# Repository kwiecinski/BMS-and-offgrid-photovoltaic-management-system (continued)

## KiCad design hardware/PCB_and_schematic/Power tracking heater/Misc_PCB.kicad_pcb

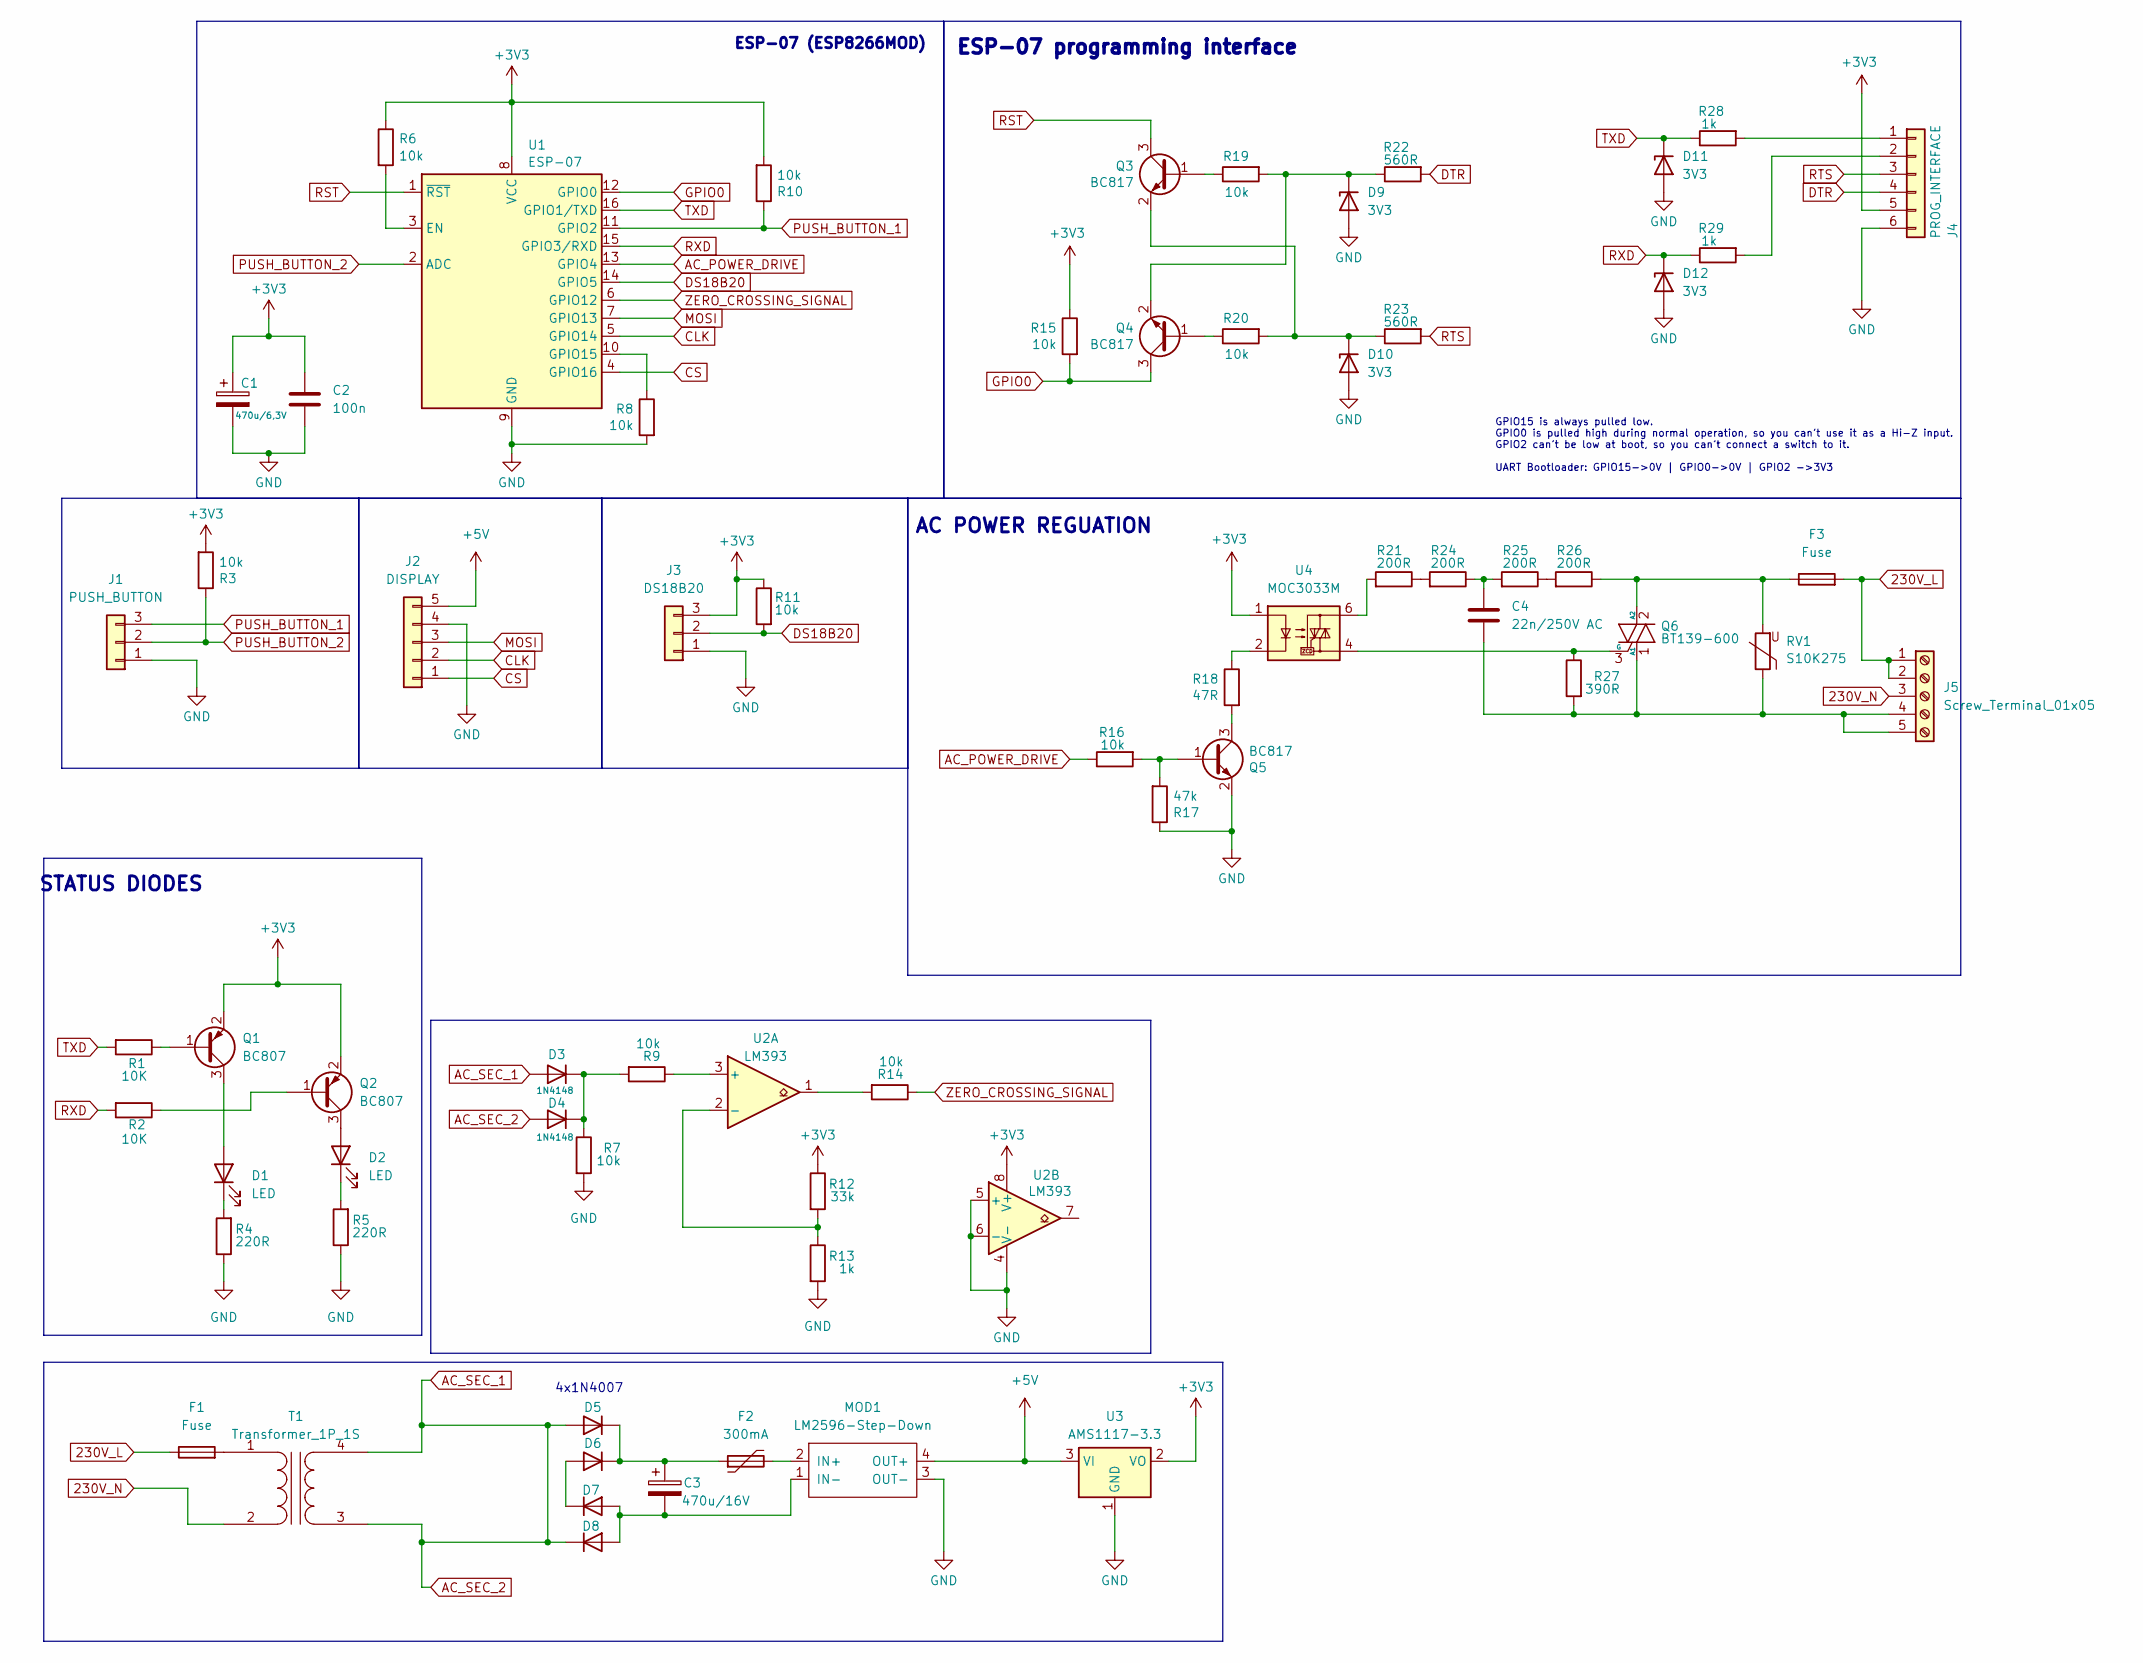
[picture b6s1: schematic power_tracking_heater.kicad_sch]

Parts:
C1: 470u/6,3V; CP_Elec_5x5.7
C2: 100n; C_0805_2012Metric
C3: 470u/16V; CP_Elec_5x5.7
C4: 22n/250V AC; C_Rect_L16.5mm_W6.0mm_P15.00mm_MKT
D1, D2: LED; LED_PLCC-2_3.4x3.0mm_KA
D3, D4: 1N4148; D_DO-35_SOD27_P7.62mm_Horizontal
D5, D6, D7, D8: 1N4007; DO-213AB_1-mediana
D9, D10, D11, D12: 3V3; D_MiniMELF
F1, F3: Fuse; Fuseholder_Clip-5x20mm_Eaton_1A5601-01_Inline_P20.80x6.76mm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
F2: 300mA; Fuse_2010_5025Metric
J1: PUSH_BUTTON; PinSocket_1x03_P2.54mm_Vertical
J2: DISPLAY; JST_XA_B05B-XASK-1_1x05_P2.50mm_Vertical
J3: DS18B20; JST_XA_B03B-XASK-1_1x03_P2.50mm_Vertical
J4: PROG_INTERFACE; Conn-01x06
J5: Screw_Terminal_01x05; Screw-Terminal-5.00mm-5pin
MOD1: LM2596-Step-Down; MP1504_Mini_3A_Step_Down_Conv
Q1, Q2: BC807; SOT-23
Q3, Q4, Q5: BC817; SOT-23
Q6: BT139-600; TO-220-3_V_Wide_Legs
R1, R2: 10K; R_0805_2012Metric_Pad1.20x1.40mm_HandSolder
R3, R7, R8, R9, R10, R11, R14, R15, R16, R19, R20: 10k; R_0805_2012Metric_Pad1.20x1.40mm_HandSolder
R4, R5: 220R; R_0805_2012Metric_Pad1.20x1.40mm_HandSolder
R6: 10k; C_0805_2012Metric
R12: 33k; R_0805_2012Metric_Pad1.20x1.40mm_HandSolder
R13, R28, R29: 1k; R_0805_2012Metric_Pad1.20x1.40mm_HandSolder
R17: 47k; R_0805_2012Metric_Pad1.20x1.40mm_HandSolder
R18: 47R; R_0805_2012Metric_Pad1.20x1.40mm_HandSolder
R21, R24, R25, R26: 200R; R_Axial_DIN0204_L3.6mm_D1.6mm_P7.62mm_Horizontal
R22, R23: 560R; R_0805_2012Metric_Pad1.20x1.40mm_HandSolder
R27: 390R; R_Axial_DIN0204_L3.6mm_D1.6mm_P5.08mm_Horizontal
RV1: S10K275; RV_Disc_D7mm_W3.5mm_P5mm
T1: Transformer_1P_1S; Transformer TS2-14
U1: ESP-07
U2: LM393; DIP-8_W7.62mm_LongPads
U3: AMS1117-3.3; SOT-223-3_TabPin2
U4: MOC3033M; DIP-6_W7.62mm_LongPads

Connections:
230V_L: F1.1, F3.2, J5.1, J5.2
230V_N: J5.3, T1.2 (AB)
+3V3: C1.1, C2.1, J3.3, J4.5, Q1.2 (E), Q2.2 (E), R3.2, R6.1, R10.2, R11.1, R12.1, R15.1, U1.8 (VCC), U2.8 (V+), U3.2 (VO), U4.1
+5V: J2.5, MOD1.4 (OUT+), U3.3 (VI)
AC_POWER_DRIVE: R16.1, U1.13 (GPIO4)
AC_SEC_1: D3.2 (A), D4.2 (A), D5.2 (A), D8.1 (K), T1.3 (SA), T1.4 (SB)
CLK: J2.2, U1.5 (GPIO14)
CS: J2.1, U1.4 (GPIO16)
DS18B20: J3.2, R11.2, U1.14 (GPIO5)
DTR: J4.4, R22.2
GND: C1.2, C2.2, D9.2 (A), D10.2 (A), D11.2 (A), D12.2 (A), J1.1, J2.4, J3.1, J4.6, MOD1.3 (OUT-), Q5.2 (E), R4.1, R5.1, R7.2, R8.2, R13.2, R17.1, U1.9 (GND), U2.4 (V-), U2.5 (+), U2.6 (-), U3.1 (GND)
GPIO0: Q4.3 (C), R15.2, U1.12 (GPIO0)
MOSI: J2.3, U1.7 (GPIO13)
unnamed: C4.1, R24.1, R25.2
unnamed: D1.2 (A), Q1.3 (C)
unnamed: D1.1 (K), R4.2
unnamed: D2.2 (A), Q2.3 (C)
unnamed: D2.1 (K), R5.2
unnamed: D3.1 (K), D4.1 (K), R7.1, R9.2
unnamed: C3.1, D5.1 (K), D6.1 (K), F2.1
unnamed: D6.2 (A), D7.1 (K)
unnamed: C3.2, D7.2 (A), D8.2 (A), MOD1.1 (IN-)
unnamed: D9.1 (K), Q4.2 (E), R19.2, R22.1
unnamed: D10.1 (K), Q3.2 (E), R20.2, R23.1
unnamed: J4.1, R28.2
unnamed: J4.2, R29.2
unnamed: C4.2, J5.4, J5.5, Q6.1 (A1), R27.2, RV1.1
unnamed: F2.2, MOD1.2 (IN+)
unnamed: Q1.1 (B), R1.1
unnamed: Q2.1 (B), R2.1
unnamed: Q3.1 (B), R19.1
unnamed: Q4.1 (B), R20.1
unnamed: Q5.1 (B), R16.2, R17.2
unnamed: Q5.3 (C), R18.2
unnamed: F3.1, Q6.2 (A2), R26.1, RV1.2
unnamed: Q6.3 (G), R27.1, U4.4
unnamed: R14.2, U2.1
unnamed: R18.1, U4.2
unnamed: R21.1, R24.2
unnamed: R21.2, U4.6
unnamed: R25.1, R26.2
unnamed: F1.2, T1.1 (AA)
unnamed: R6.2, U1.3 (EN)
unnamed: R8.1, U1.10 (GPIO15)
unnamed: R9.1, U2.3 (+)
unnamed: R12.2, R13.1, U2.2 (-)
PUSH_BUTTON_1: J1.3, R10.1, U1.11 (GPIO2)
PUSH_BUTTON_2: J1.2, R3.1, U1.2 (ADC)
RST: Q3.3 (C), U1.1 (~RST)
RTS: J4.3, R23.2
RXD: D12.1 (K), R2.2, R29.1, U1.15 (GPIO3/RXD)
TXD: D11.1 (K), R1.2, R28.1, U1.16 (GPIO1/TXD)
ZERO_CROSSING_SIGNAL: R14.1, U1.6 (GPIO12)

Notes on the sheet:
ESP-07 (ESP8266MOD)
STATUS DIODES
4x1N4007
GPIO15 is always pulled low. GPIO0 is pulled high during normal operation, so you can’t use it as a Hi-Z input. GPIO2 can’t be low at boot, so you can’t connect a switch to it. UART Bootloader: GPIO15->0V | GPIO0->0V | GPIO2 ->3V3
ESP-07 programming interface
AC POWER REGUATION

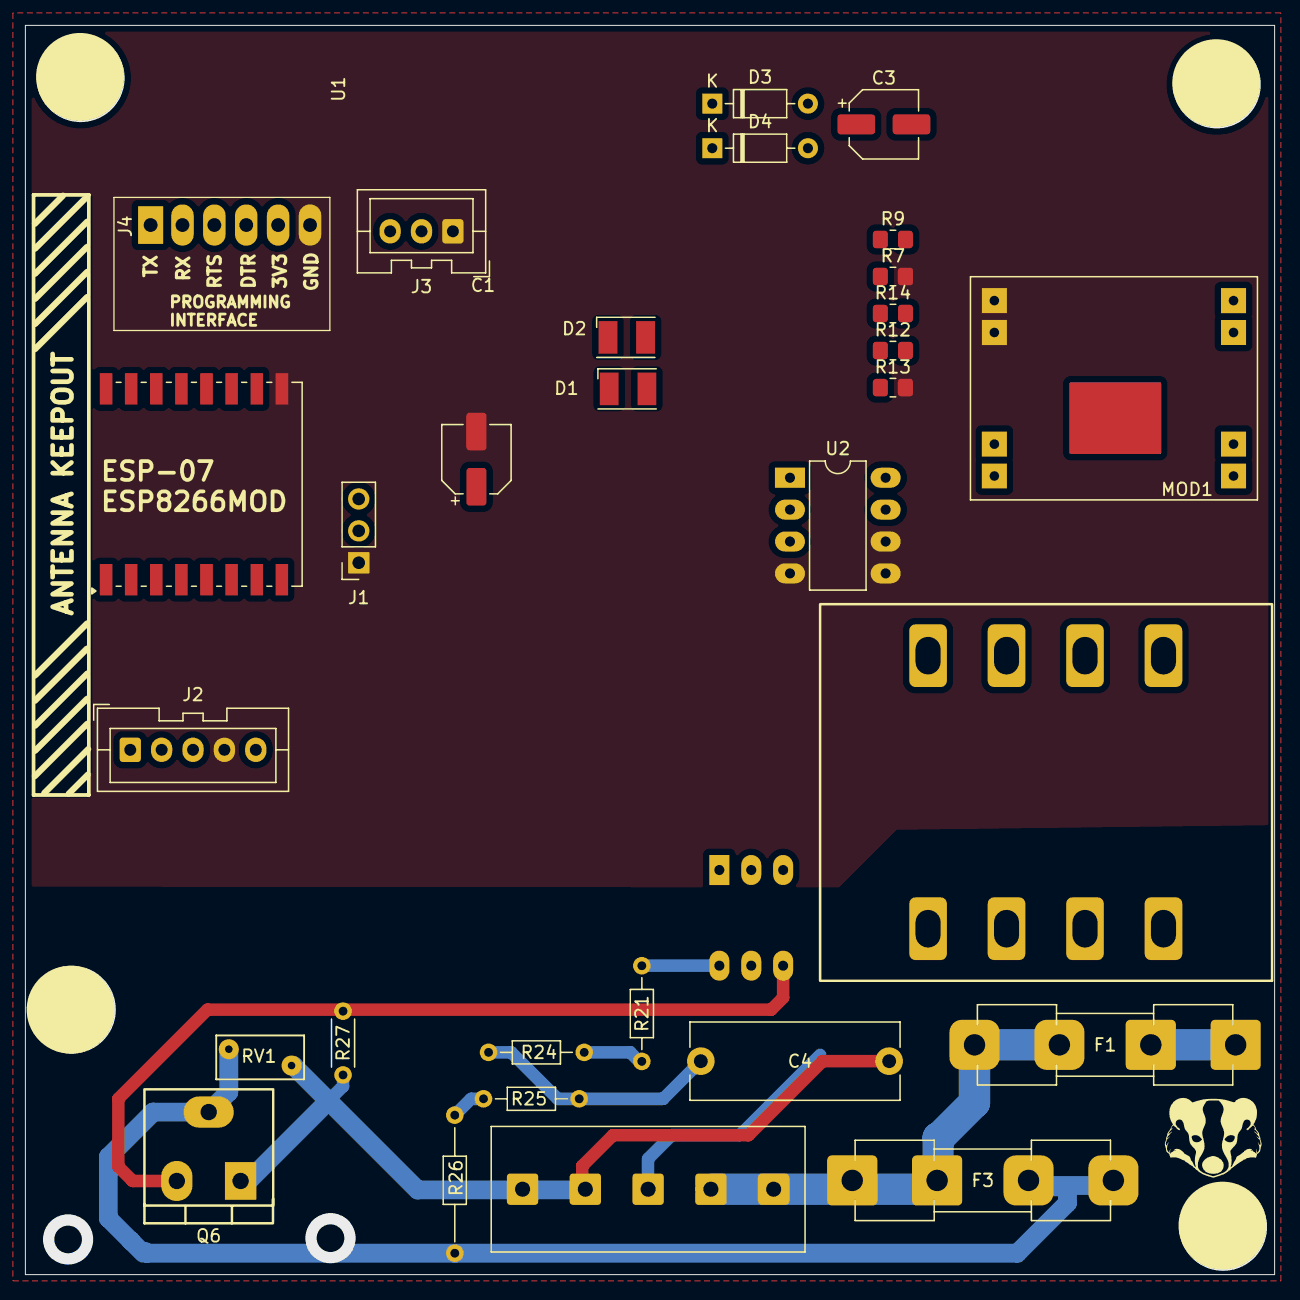
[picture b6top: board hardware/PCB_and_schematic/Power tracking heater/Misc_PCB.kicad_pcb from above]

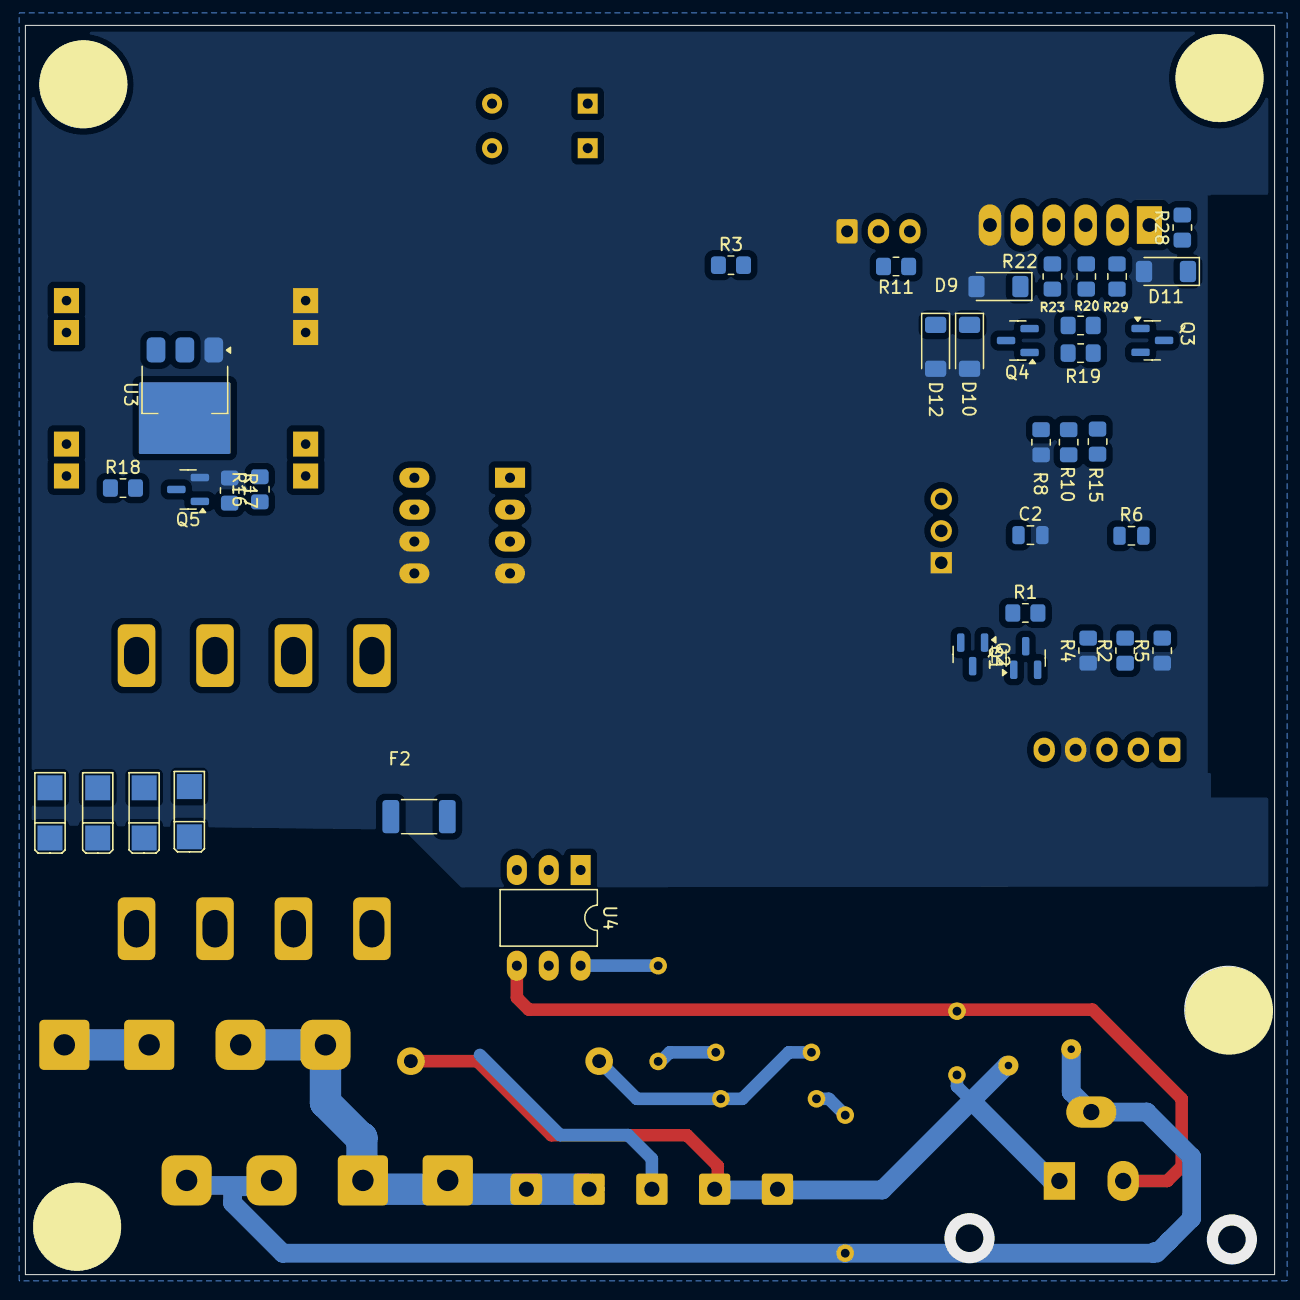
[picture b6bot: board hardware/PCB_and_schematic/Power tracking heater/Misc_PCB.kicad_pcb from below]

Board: 2 copper layers, 99.5 x 99.5 mm, 66 parts (36 on the bottom side), 53 nets.

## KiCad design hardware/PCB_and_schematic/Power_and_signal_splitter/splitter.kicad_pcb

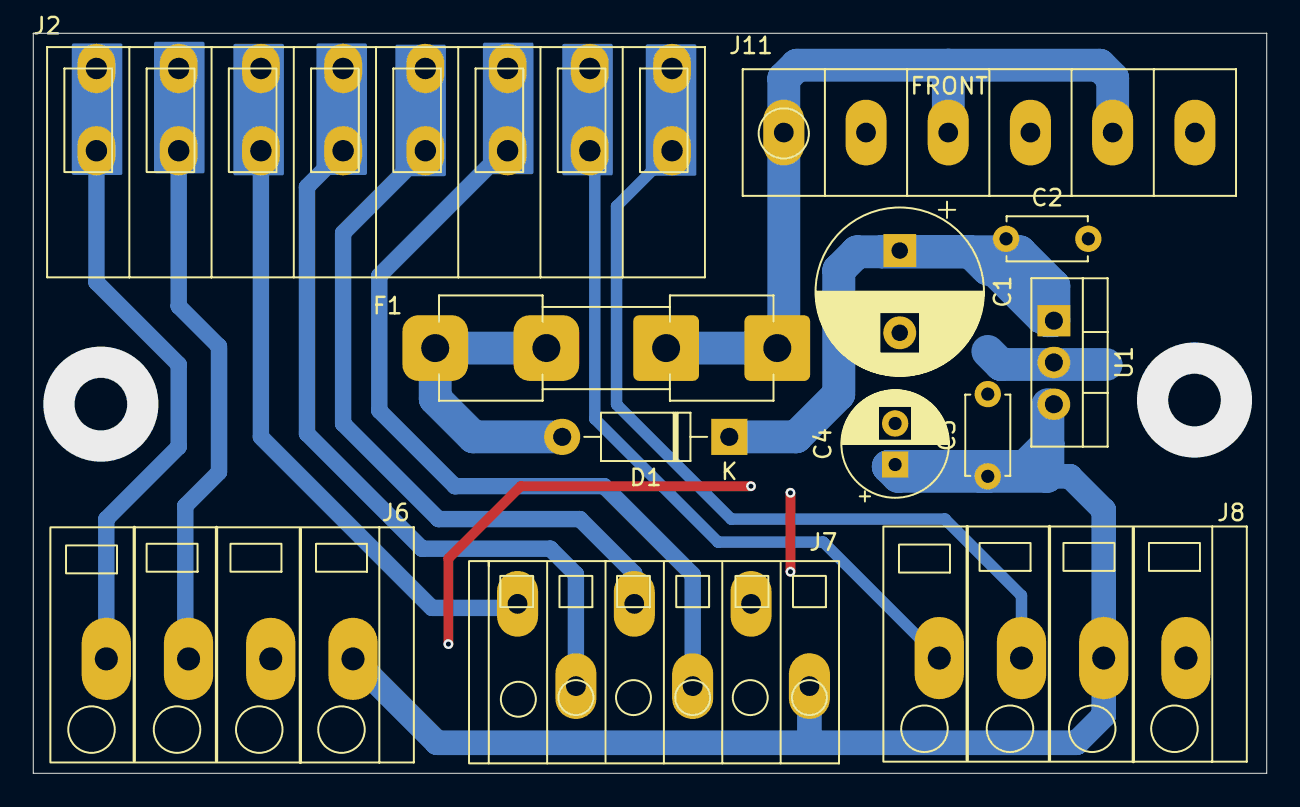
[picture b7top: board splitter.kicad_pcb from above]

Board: 2 copper layers, 75.0 x 45.0 mm, 12 parts (0 on the bottom side), 13 nets.

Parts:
C1: 1000u/35V; CP_Radial_D10.0mm_P5.00mm
C2, C3: 100n; C_Disc_D4.7mm_W2.5mm_P5.00mm
C4: 100u/16V; CP_Radial_D6.3mm_P2.50mm
D1: 1N4007; D_DO-41_SOD81_P10.16mm_Horizontal
F1: Fuse; Fuseholder_Clip-5x20mm_Eaton_1A5601-01_Inline_P20.80x6.76mm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
J2: SIGNAL_TERMINAL; WAGO-255-8P
J6: DIODE_PROBE; WAGO-739-4P
J7: OPTICAL_PROBE; HDQ-250-6P
J8: UNUSED; WAGO-739-4P
J11: POWER_SUPPLY; Screw-Terminal-P6-rast-5mm-6,7x30
U1: L7812; TO-220-3_Vertical

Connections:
+12V: C3.1, C4.1, J6.1, J7.1, J8.2, U1.3 (OUT)
DIODE_PROBE_RX: J2.2, J6.3
DIODE_PROBE_TX: J2.1, J6.4
GND: C1.2, C2.2, C3.2, C4.2, J6.2, J7.2, J8.1, J11.2, J11.4, J11.6, U1.2 (GND)
unnamed: D1.2 (A), F1.1
unnamed: F1.2, J11.1, J11.3, J11.5
OPTICAL_PROBE_RX_A: J2.5, J7.4
OPTICAL_PROBE_RX_B: J2.6, J7.3
OPTICAL_PROBE_TX_A: J2.3, J7.6
OPTICAL_PROBE_TX_B: J2.4, J7.5
UNUSED_T1: J2.7, J8.4
UNUSED_T2: J2.8, J8.3
VDD: C1.1, C2.1, D1.1 (K), U1.1 (IN)
